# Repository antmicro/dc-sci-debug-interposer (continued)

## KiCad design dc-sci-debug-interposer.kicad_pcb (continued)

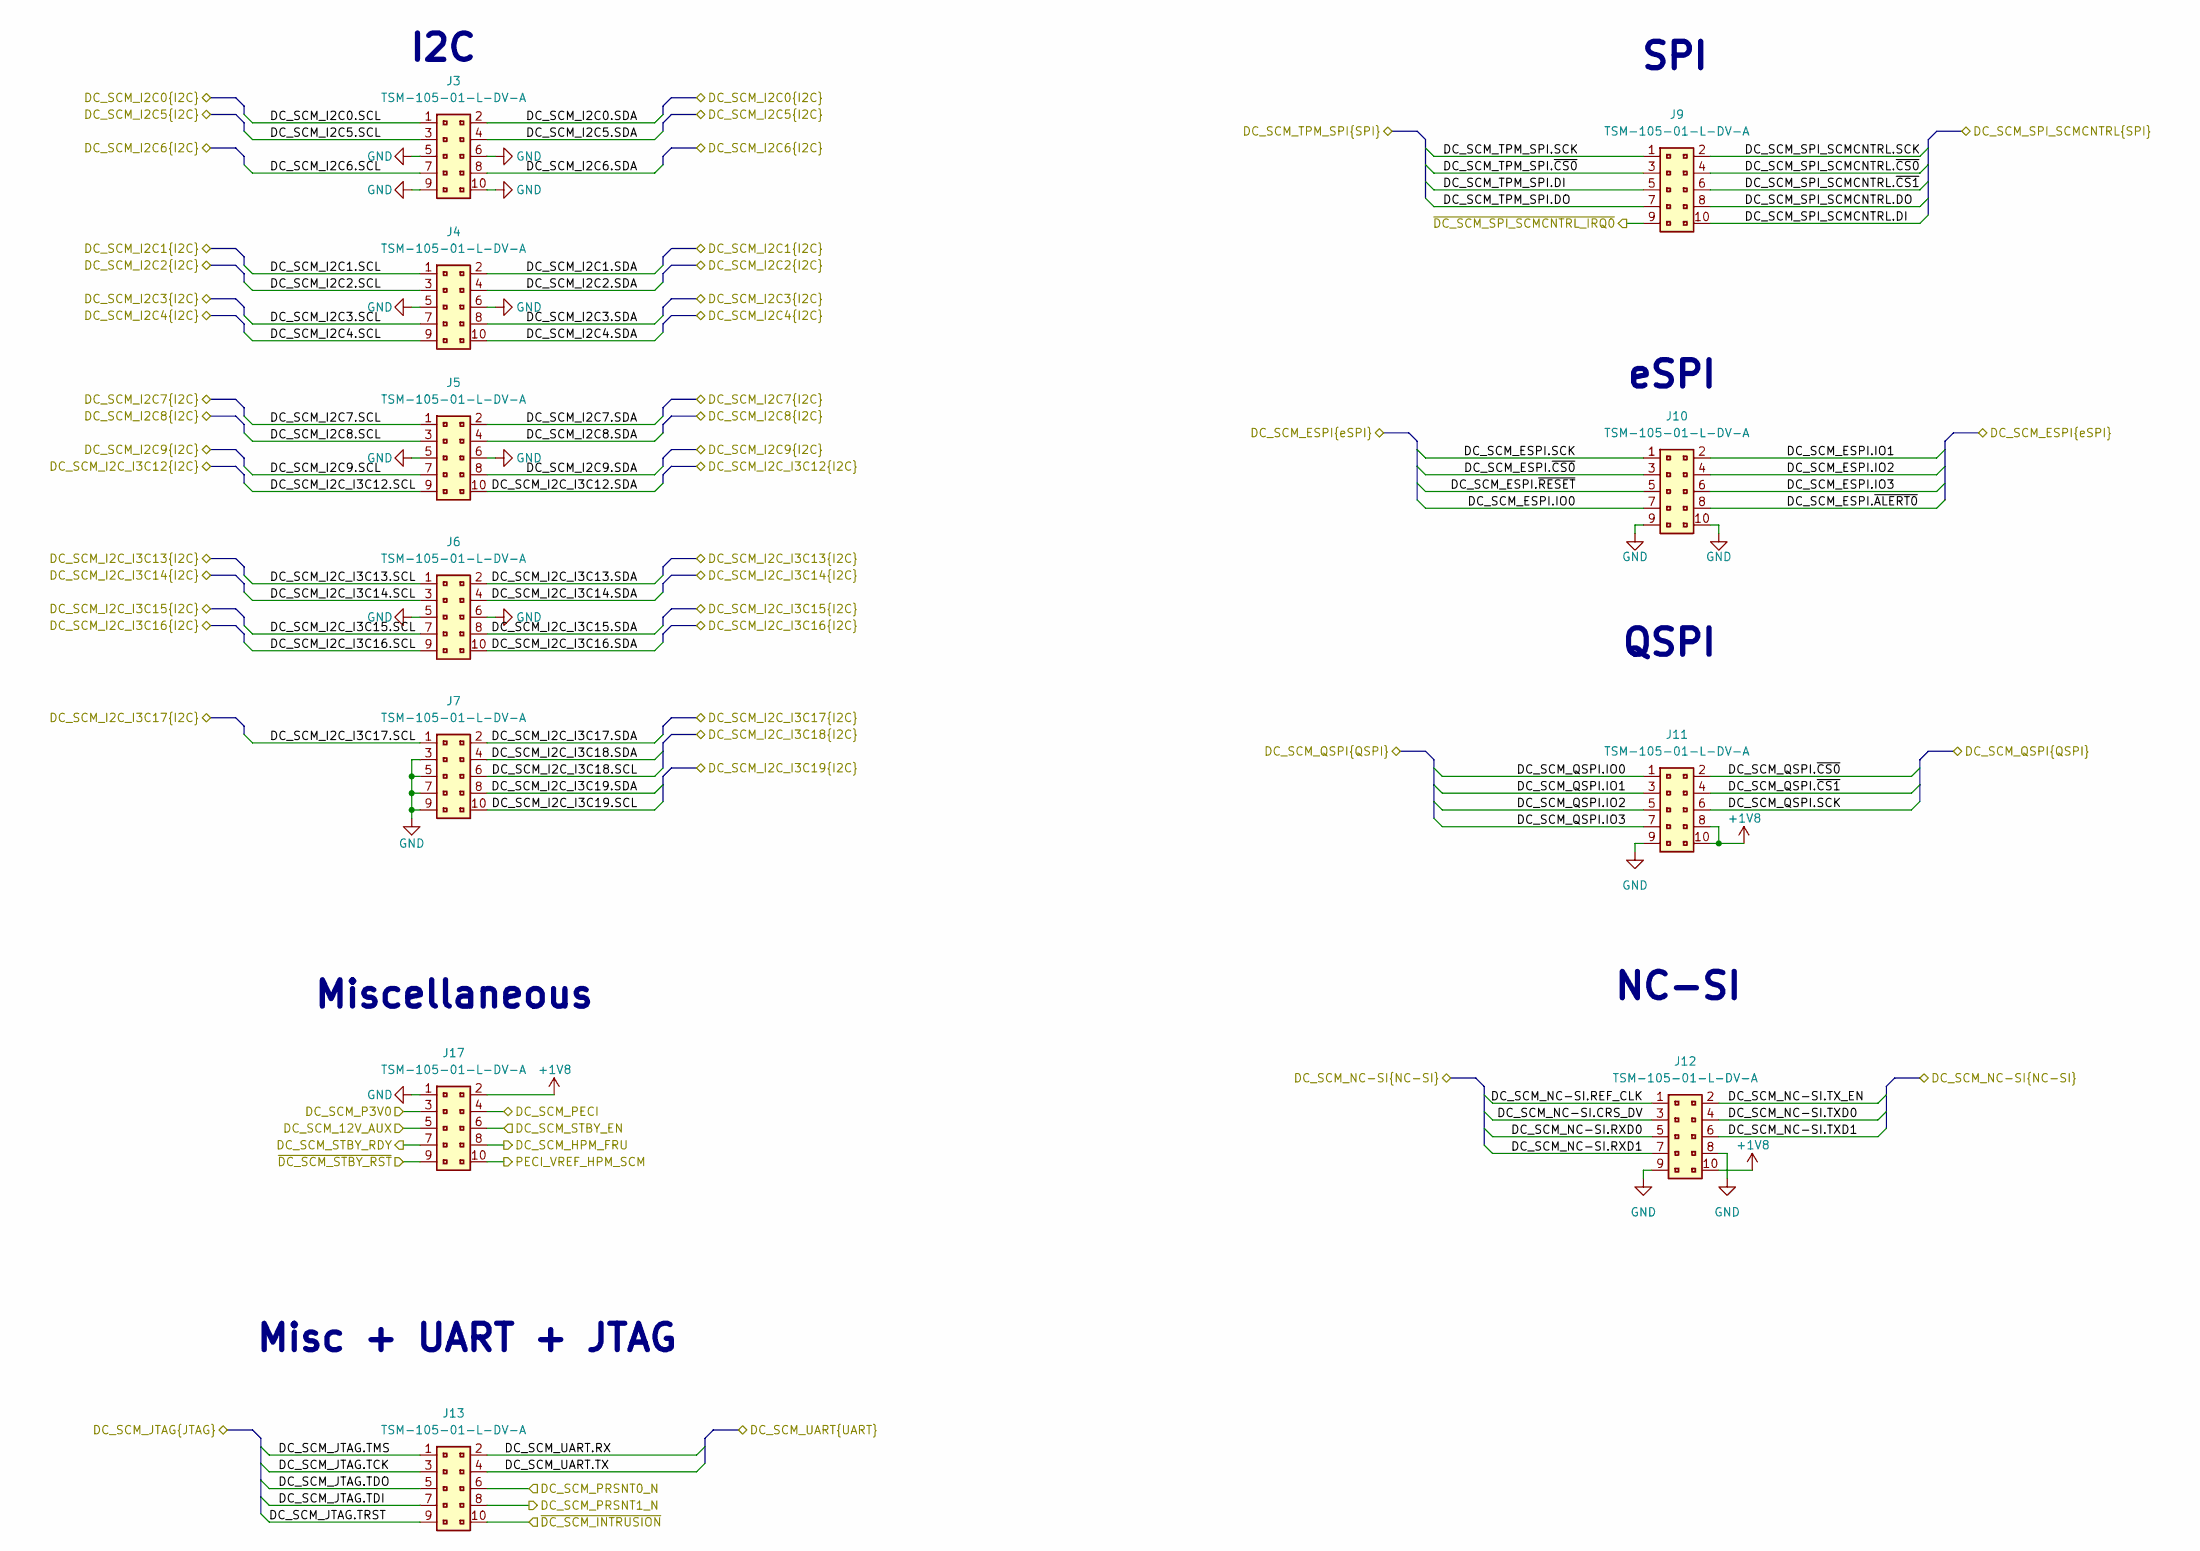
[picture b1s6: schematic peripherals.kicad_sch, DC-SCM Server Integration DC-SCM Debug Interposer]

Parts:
J3, J4, J5, J6, J7, J9, J10, J11, J12, J13, J17: PinHeader_2x5_P2.54mm_SMD; MPN TSM-105-01-L-DV-A

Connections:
+1V8: J11.8, J11.10, J12.10, J17.2; also elsewhere on the board
/DC-SCI edge connector/DC_SCM_12V_AUX: J17.5; also elsewhere on the board
/DC-SCI edge connector/DC_SCM_ESPI.IO0: J10.7; also elsewhere on the board
/DC-SCI edge connector/DC_SCM_ESPI.IO1: J10.2; also elsewhere on the board
/DC-SCI edge connector/DC_SCM_ESPI.IO2: J10.4; also elsewhere on the board
/DC-SCI edge connector/DC_SCM_ESPI.IO3: J10.6; also elsewhere on the board
/DC-SCI edge connector/DC_SCM_ESPI.SCK: J10.1; also elsewhere on the board
/DC-SCI edge connector/DC_SCM_ESPI.~ALERT0: J10.8; also elsewhere on the board
/DC-SCI edge connector/DC_SCM_ESPI.~CS0: J10.3; also elsewhere on the board
/DC-SCI edge connector/DC_SCM_ESPI.~RESET: J10.5; also elsewhere on the board
/DC-SCI edge connector/DC_SCM_HPM_FRU: J17.8; also elsewhere on the board
/DC-SCI edge connector/DC_SCM_I2C0.SCL: J3.1; also elsewhere on the board
/DC-SCI edge connector/DC_SCM_I2C0.SDA: J3.2; also elsewhere on the board
/DC-SCI edge connector/DC_SCM_I2C1.SCL: J4.1; also elsewhere on the board
/DC-SCI edge connector/DC_SCM_I2C1.SDA: J4.2; also elsewhere on the board
/DC-SCI edge connector/DC_SCM_I2C2.SCL: J4.3; also elsewhere on the board
/DC-SCI edge connector/DC_SCM_I2C2.SDA: J4.4; also elsewhere on the board
/DC-SCI edge connector/DC_SCM_I2C3.SCL: J4.7; also elsewhere on the board
/DC-SCI edge connector/DC_SCM_I2C3.SDA: J4.8; also elsewhere on the board
/DC-SCI edge connector/DC_SCM_I2C4.SCL: J4.9; also elsewhere on the board
/DC-SCI edge connector/DC_SCM_I2C4.SDA: J4.10; also elsewhere on the board
/DC-SCI edge connector/DC_SCM_I2C5.SCL: J3.3; also elsewhere on the board
/DC-SCI edge connector/DC_SCM_I2C5.SDA: J3.4; also elsewhere on the board
/DC-SCI edge connector/DC_SCM_I2C6.SCL: J3.7; also elsewhere on the board
/DC-SCI edge connector/DC_SCM_I2C6.SDA: J3.8; also elsewhere on the board
/DC-SCI edge connector/DC_SCM_I2C7.SCL: J5.1; also elsewhere on the board
/DC-SCI edge connector/DC_SCM_I2C7.SDA: J5.2; also elsewhere on the board
/DC-SCI edge connector/DC_SCM_I2C8.SCL: J5.3; also elsewhere on the board
/DC-SCI edge connector/DC_SCM_I2C8.SDA: J5.4; also elsewhere on the board
/DC-SCI edge connector/DC_SCM_I2C9.SCL: J5.7; also elsewhere on the board
/DC-SCI edge connector/DC_SCM_I2C9.SDA: J5.8; also elsewhere on the board
/DC-SCI edge connector/DC_SCM_I2C_I3C12.SCL: J5.9; also elsewhere on the board
/DC-SCI edge connector/DC_SCM_I2C_I3C12.SDA: J5.10; also elsewhere on the board
/DC-SCI edge connector/DC_SCM_I2C_I3C13.SCL: J6.1; also elsewhere on the board
/DC-SCI edge connector/DC_SCM_I2C_I3C13.SDA: J6.2; also elsewhere on the board
/DC-SCI edge connector/DC_SCM_I2C_I3C14.SCL: J6.3; also elsewhere on the board
/DC-SCI edge connector/DC_SCM_I2C_I3C14.SDA: J6.4; also elsewhere on the board
/DC-SCI edge connector/DC_SCM_I2C_I3C15.SCL: J6.7; also elsewhere on the board
/DC-SCI edge connector/DC_SCM_I2C_I3C15.SDA: J6.8; also elsewhere on the board
/DC-SCI edge connector/DC_SCM_I2C_I3C16.SCL: J6.9; also elsewhere on the board
/DC-SCI edge connector/DC_SCM_I2C_I3C16.SDA: J6.10; also elsewhere on the board
/DC-SCI edge connector/DC_SCM_I2C_I3C17.SCL: J7.1; also elsewhere on the board
/DC-SCI edge connector/DC_SCM_I2C_I3C17.SDA: J7.2; also elsewhere on the board
/DC-SCI edge connector/DC_SCM_I2C_I3C18.SCL: J7.6; also elsewhere on the board
/DC-SCI edge connector/DC_SCM_I2C_I3C18.SDA: J7.4; also elsewhere on the board
/DC-SCI edge connector/DC_SCM_I2C_I3C19.SCL: J7.10; also elsewhere on the board
/DC-SCI edge connector/DC_SCM_I2C_I3C19.SDA: J7.8; also elsewhere on the board
/DC-SCI edge connector/DC_SCM_JTAG.TCK: J13.3; also elsewhere on the board
/DC-SCI edge connector/DC_SCM_JTAG.TDI: J13.7; also elsewhere on the board
/DC-SCI edge connector/DC_SCM_JTAG.TDO: J13.5; also elsewhere on the board
/DC-SCI edge connector/DC_SCM_JTAG.TMS: J13.1; also elsewhere on the board
/DC-SCI edge connector/DC_SCM_JTAG.TRST: J13.9; also elsewhere on the board
/DC-SCI edge connector/DC_SCM_NC-SI.CRS_DV: J12.3; also elsewhere on the board
/DC-SCI edge connector/DC_SCM_NC-SI.REF_CLK: J12.1; also elsewhere on the board
/DC-SCI edge connector/DC_SCM_NC-SI.RXD0: J12.5; also elsewhere on the board
/DC-SCI edge connector/DC_SCM_NC-SI.RXD1: J12.7; also elsewhere on the board
/DC-SCI edge connector/DC_SCM_NC-SI.TXD0: J12.4; also elsewhere on the board
/DC-SCI edge connector/DC_SCM_NC-SI.TXD1: J12.6; also elsewhere on the board
/DC-SCI edge connector/DC_SCM_NC-SI.TX_EN: J12.2; also elsewhere on the board
/DC-SCI edge connector/DC_SCM_P3V0: J17.3; also elsewhere on the board
/DC-SCI edge connector/DC_SCM_PECI: J17.4; also elsewhere on the board
/DC-SCI edge connector/DC_SCM_PRSNT0_N: J13.6; also elsewhere on the board
/DC-SCI edge connector/DC_SCM_PRSNT1_N: J13.8; also elsewhere on the board
/DC-SCI edge connector/DC_SCM_QSPI.IO0: J11.1; also elsewhere on the board
/DC-SCI edge connector/DC_SCM_QSPI.IO1: J11.3; also elsewhere on the board
/DC-SCI edge connector/DC_SCM_QSPI.IO2: J11.5; also elsewhere on the board
/DC-SCI edge connector/DC_SCM_QSPI.IO3: J11.7; also elsewhere on the board
/DC-SCI edge connector/DC_SCM_QSPI.SCK: J11.6; also elsewhere on the board
/DC-SCI edge connector/DC_SCM_QSPI.~CS0: J11.2; also elsewhere on the board
/DC-SCI edge connector/DC_SCM_QSPI.~CS1: J11.4; also elsewhere on the board
/DC-SCI edge connector/DC_SCM_SPI_SCMCNTRL.DI: J9.10; also elsewhere on the board
/DC-SCI edge connector/DC_SCM_SPI_SCMCNTRL.DO: J9.8; also elsewhere on the board
/DC-SCI edge connector/DC_SCM_SPI_SCMCNTRL.SCK: J9.2; also elsewhere on the board
/DC-SCI edge connector/DC_SCM_SPI_SCMCNTRL.~CS0: J9.4; also elsewhere on the board
/DC-SCI edge connector/DC_SCM_SPI_SCMCNTRL.~CS1: J9.6; also elsewhere on the board
/DC-SCI edge connector/DC_SCM_STBY_EN: J17.6; also elsewhere on the board
/DC-SCI edge connector/DC_SCM_STBY_RDY: J17.7; also elsewhere on the board
/DC-SCI edge connector/DC_SCM_TPM_SPI.DI: J9.5; also elsewhere on the board
/DC-SCI edge connector/DC_SCM_TPM_SPI.DO: J9.7; also elsewhere on the board
/DC-SCI edge connector/DC_SCM_TPM_SPI.SCK: J9.1; also elsewhere on the board
/DC-SCI edge connector/DC_SCM_TPM_SPI.~CS0: J9.3; also elsewhere on the board
/DC-SCI edge connector/DC_SCM_UART.RX: J13.2; also elsewhere on the board
/DC-SCI edge connector/DC_SCM_UART.TX: J13.4; also elsewhere on the board
/DC-SCI edge connector/PECI_VREF_HPM_SCM: J17.10; also elsewhere on the board
/DC-SCI edge connector/~DC_SCM_INTRUSION: J13.10; also elsewhere on the board
/DC-SCI edge connector/~DC_SCM_SPI_SCMCNTRL_IRQ0: J9.9; also elsewhere on the board
/DC-SCI edge connector/~DC_SCM_STBY_RST: J17.9; also elsewhere on the board
GND: J3.5, J3.6, J3.9, J3.10, J4.5, J4.6, J5.5, J5.6, J6.5, J6.6, J7.3, J7.5, J7.7, J7.9, J10.9, J10.10, J11.9, J12.8, J12.9, J17.1; also elsewhere on the board

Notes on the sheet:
I2C
SPI
NC-SI
Misc + UART + JTAG
Miscellaneous
eSPI
QSPI

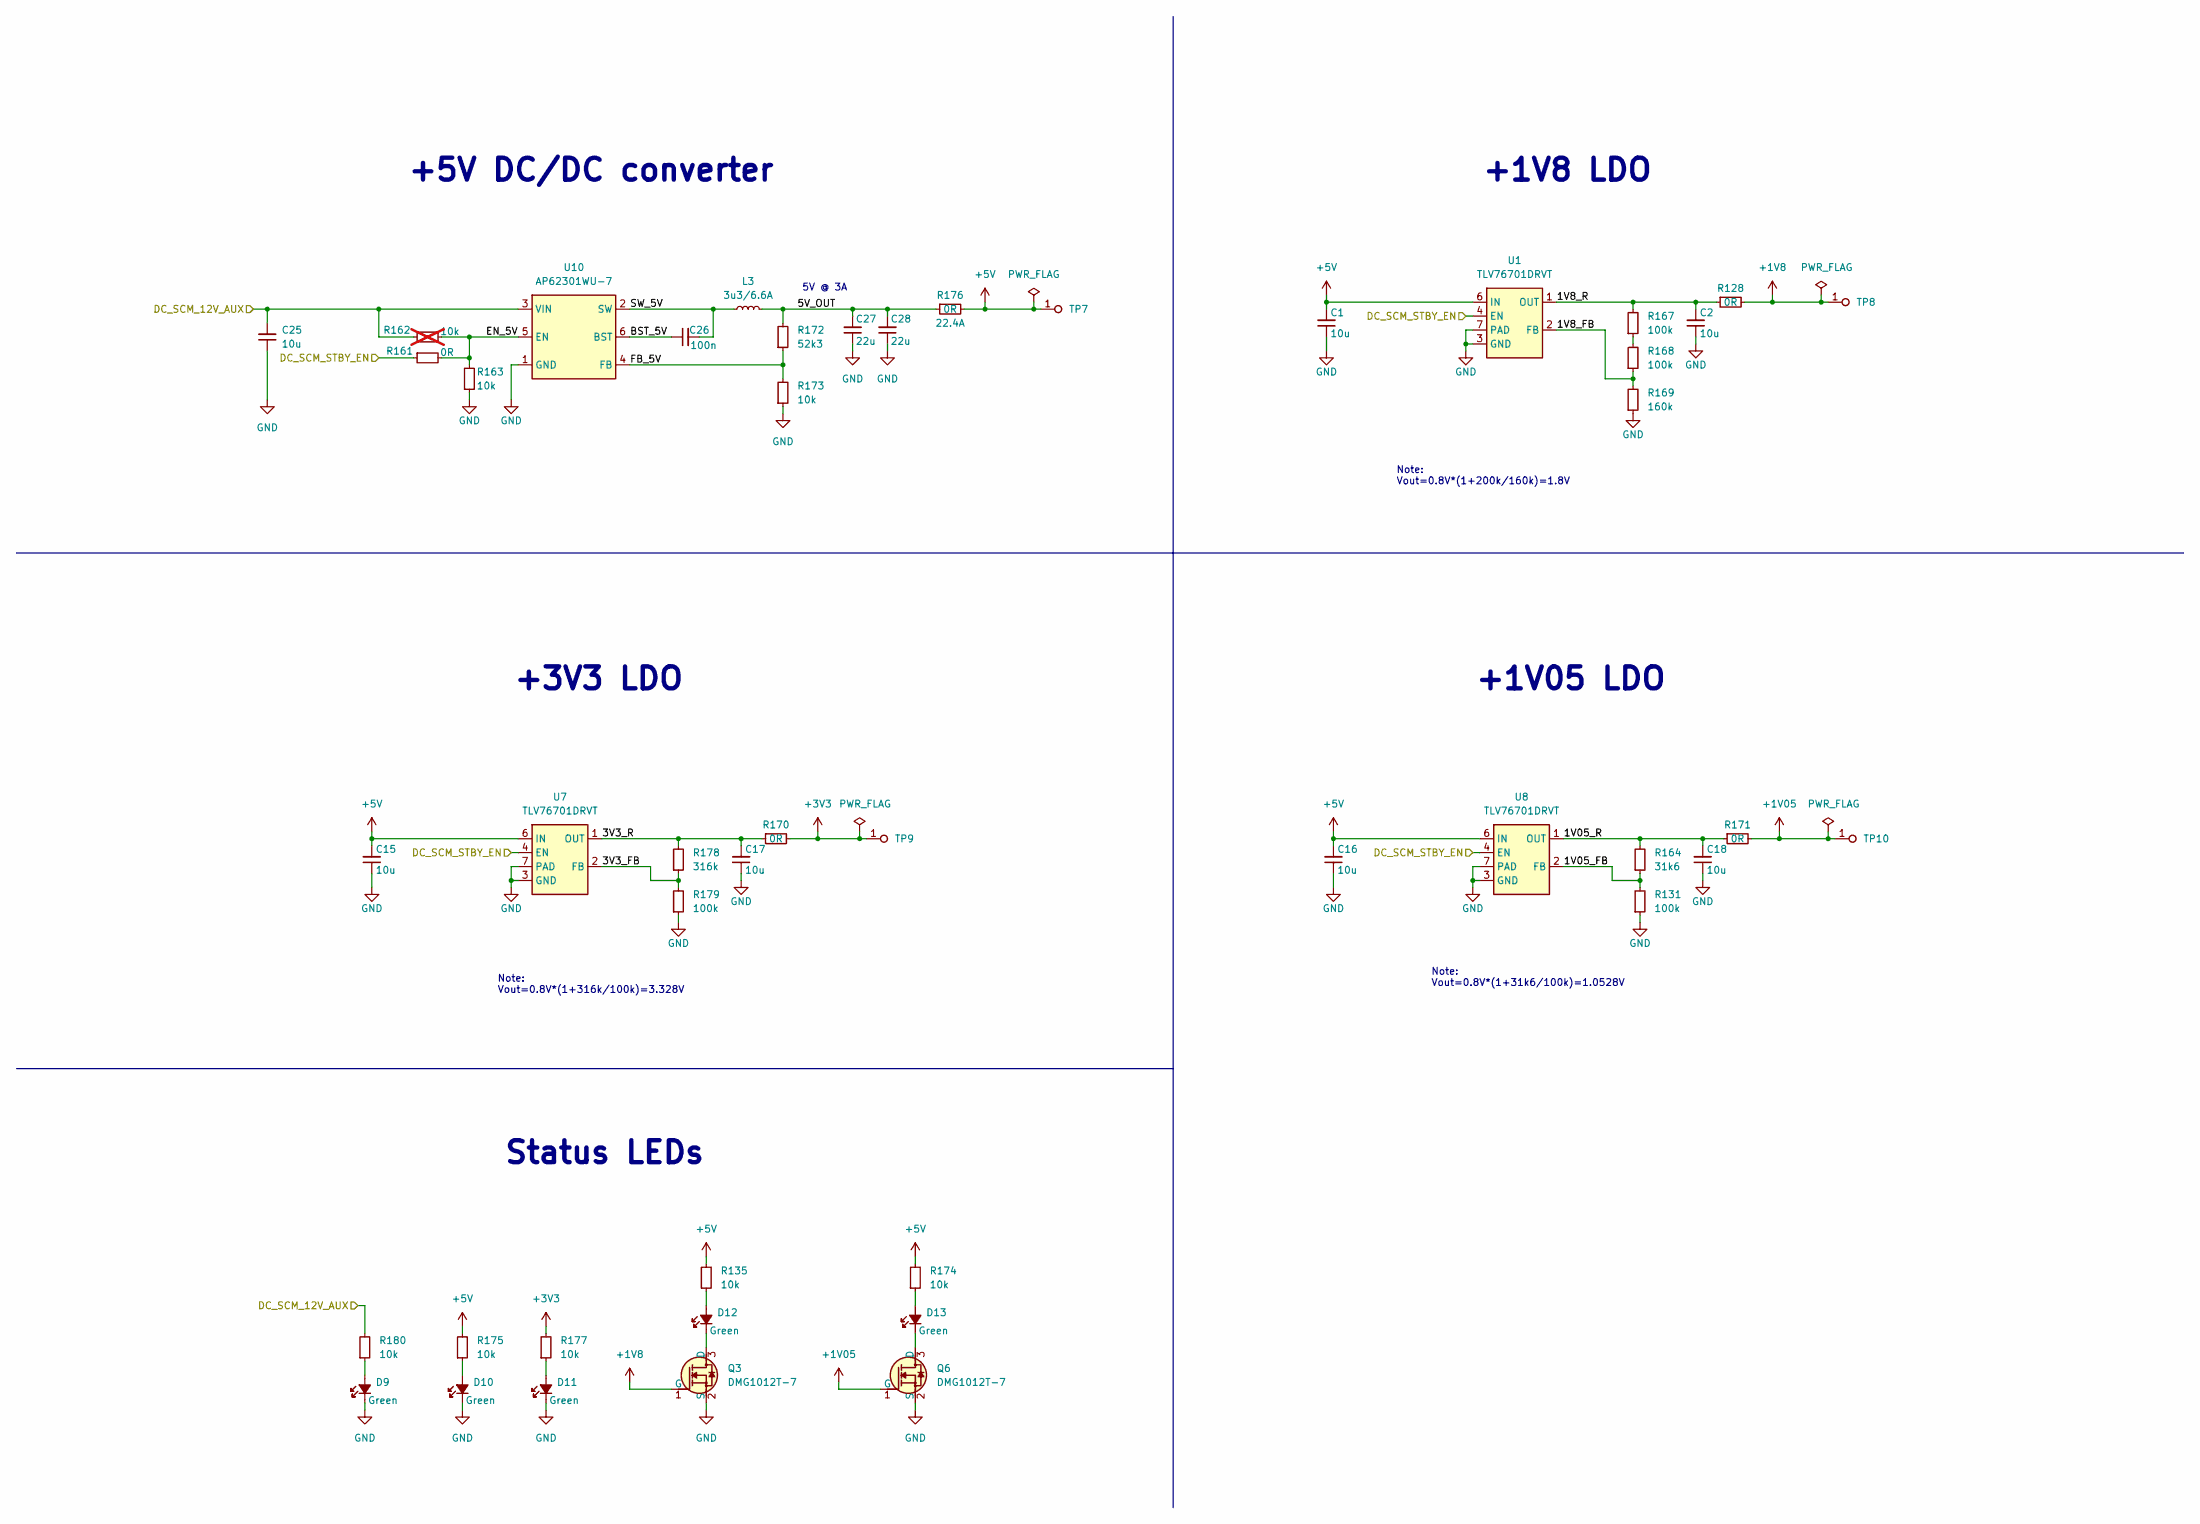
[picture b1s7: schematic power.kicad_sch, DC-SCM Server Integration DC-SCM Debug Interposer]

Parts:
C1, C2, C15, C16, C17, C18: C_10u_10V_0402; C_0402_1005Metric; Voltage 10V; MPN GRM155R61A106ME11D
C25: C_10u_16V_0603; C_0603_1608Metric; Voltage 16V; MPN GRM188C81C106MA73D
C26: C_100n_50V_X8L_0402; C_0402_1005Metric; Voltage 50V; MPN GCM155L8EH104KE07D
C27: C_22u_16V_0603; C_0603_1608Metric_EIA; Voltage 16V; MPN CL10A226MO7JZNC
C28: C_22u_0603; C_0603_1608Metric; MPN GRM188R60J226MEA0D
D9, D10, D11, D12, D13: LED_G_0603_LTST-C190GKT; LED_0603_1608Metric_G; MPN LTST-C190GKT
L3: L_3u3_6.6A_XEL4030; L_Coilcraft-XEL4030; MPN XEL4030-332MEC
Q3, Q6: DMG1012T-7; SOT-523; MPN DMG1012T-7
R128, R161, R170, R171: R_0R_0402; R_0402_1005Metric; MPN ERJ2GE0R00X
R131, R167, R168, R179: R_100k_0402; R_0402_1005Metric; Tolerance 1%; MPN CR0402-FX-1003GLF
R135, R163, R173, R174, R175, R177, R180: R_10k_0402; R_0402_1005Metric; Tolerance 1%; MPN CR0402-FX-1002GLF
R162: R_10k_0402; R_0402_1005Metric; Tolerance 1%; MPN CR0402-FX-1002GLF; not fitted
R164: R_31k6_0402; R_0402_1005Metric; Tolerance 1%; MPN CR0402-FX-3162GLF
R169: R_160k_0402; R_0402_1005Metric; Tolerance 1%; MPN CR0402-FX-1603GLF
R172: R_52k3_0402; R_0402_1005Metric; Tolerance 1%; MPN CR0402-FX-5232GLF
R176: R_0R_22.4A_0603; R_0603_1608Metric; Tolerance template_tolerance; MPN PMR03EZPJ000
R178: R_316k_0402; R_0402_1005Metric; Tolerance 1%; MPN CR0402-FX-3163GLF
TP7, TP8, TP9, TP10: TP_0.75mm_SMD; TP_SMD_0.75mm
U1, U7, U8: TLV76701_WSON; WSON-6-1EP_2x2mm_P0.65mm; MPN TLV76701DRVT
U10: AP62301_TSOT; TSOT23-6; MPN AP62301WU-7

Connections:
+1V05: Q6.1 (G), R171.2, TP10.1 (1_1); also elsewhere on the board
+1V8: Q3.1 (G), R128.2, TP8.1 (1_1); also elsewhere on the board
+3V3: R170.2, R177.2, TP9.1 (1_1); also elsewhere on the board
+5V: C1.2, C15.2, C16.2, R135.2, R174.2, R175.2, R176.2, TP7.1 (1_1), U1.6 (IN), U7.6 (IN), U8.6 (IN); also elsewhere on the board
/DC-SCI edge connector/DC_SCM_12V_AUX: C25.2, R162.2, R180.2, U10.3 (VIN); also elsewhere on the board
/DC-SCI edge connector/DC_SCM_STBY_EN: R161.1, U1.4 (EN), U7.4 (EN), U8.4 (EN); also elsewhere on the board
/Power/1V05_FB: R131.2, R164.1, U8.2 (FB)
/Power/1V05_R: C18.2, R164.2, R171.1, U8.1 (OUT)
/Power/1V8_FB: R168.1, R169.2, U1.2 (FB)
/Power/1V8_R: C2.2, R128.1, R167.2, U1.1 (OUT)
/Power/3V3_FB: R178.1, R179.2, U7.2 (FB)
/Power/3V3_R: C17.2, R170.1, R178.2, U7.1 (OUT)
/Power/5V_OUT: C27.2, C28.2, L3.2, R172.2, R176.1
/Power/BST_5V: C26.1, U10.6 (BST)
/Power/EN_5V: R161.2, R162.1, R163.2, U10.5 (EN)
/Power/FB_5V: R172.1, R173.2, U10.4 (FB)
/Power/SW_5V: C26.2, L3.1, U10.2 (SW)
GND: C1.1, C2.1, C15.1, C16.1, C17.1, C18.1, C25.1, C27.1, C28.1, D9.1 (C), D10.1 (C), D11.1 (C), Q3.2 (S), Q6.2 (S), R131.1, R163.1, R169.1, R173.1, R179.1, U1.3 (GND), U1.5 (GND), U1.7 (PAD), U7.3 (GND), U7.5 (GND), U7.7 (PAD), U8.3 (GND), U8.5 (GND), U8.7 (PAD), U10.1 (GND); also elsewhere on the board
unnamed: D9.2 (A), R180.1
unnamed: D10.2 (A), R175.1
unnamed: D11.2 (A), R177.1
unnamed: D12.2 (A), R135.1
unnamed: D12.1 (C), Q3.3 (D)
unnamed: D13.2 (A), R174.1
unnamed: D13.1 (C), Q6.3 (D)
unnamed: R167.1, R168.2

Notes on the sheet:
Note: Vout=0.8V*(1+31k6/100k)=1.0528V
Note: Vout=0.8V*(1+316k/100k)=3.328V
+1V8 LDO
Status LEDs
+5V DC/DC converter
5V @ 3A
+1V05 LDO
+3V3 LDO
Note: Vout=0.8V*(1+200k/160k)=1.8V

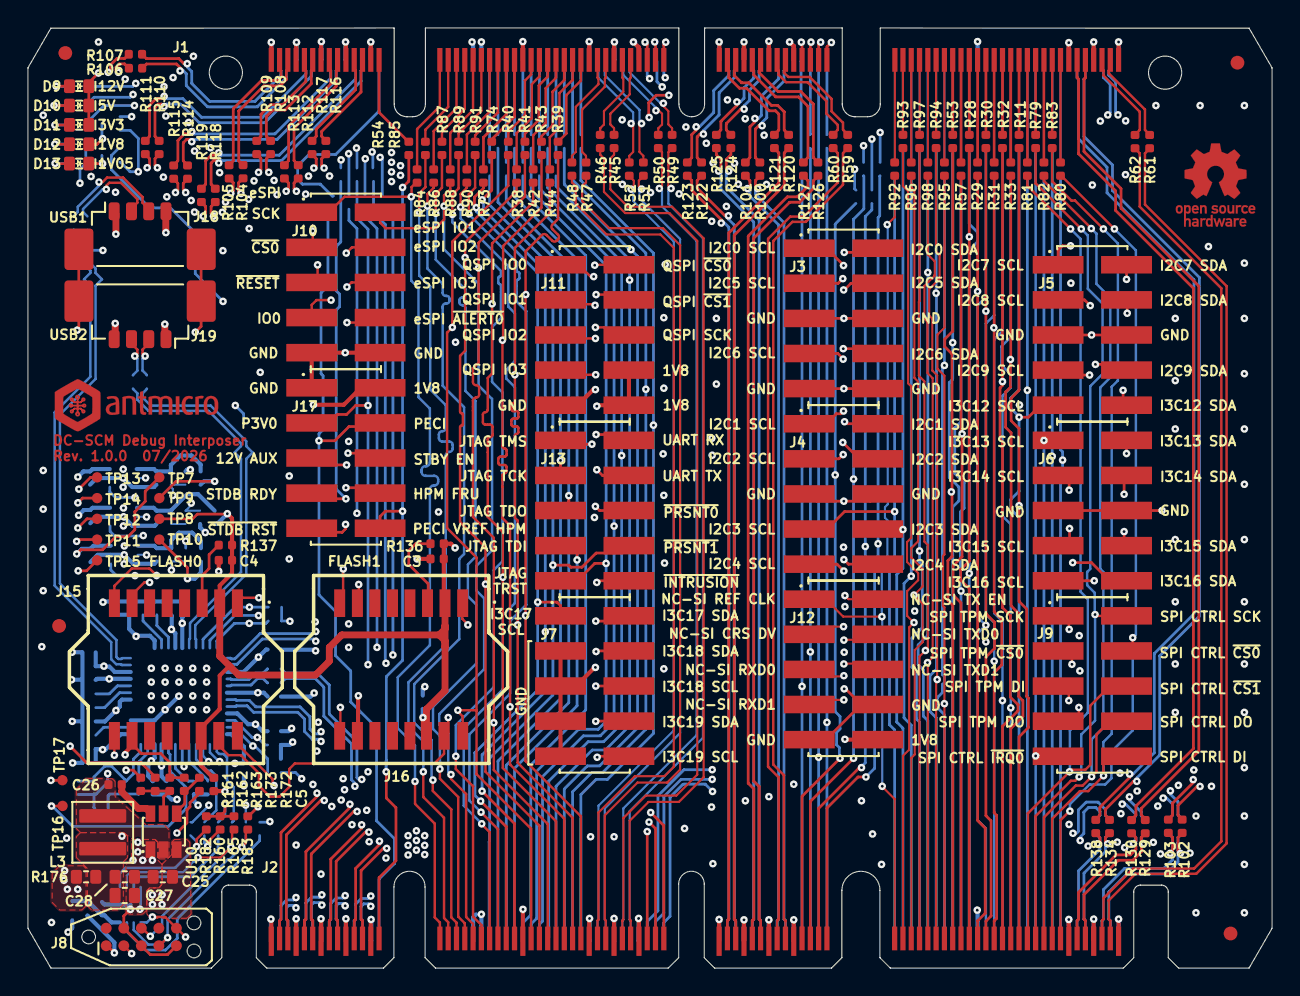
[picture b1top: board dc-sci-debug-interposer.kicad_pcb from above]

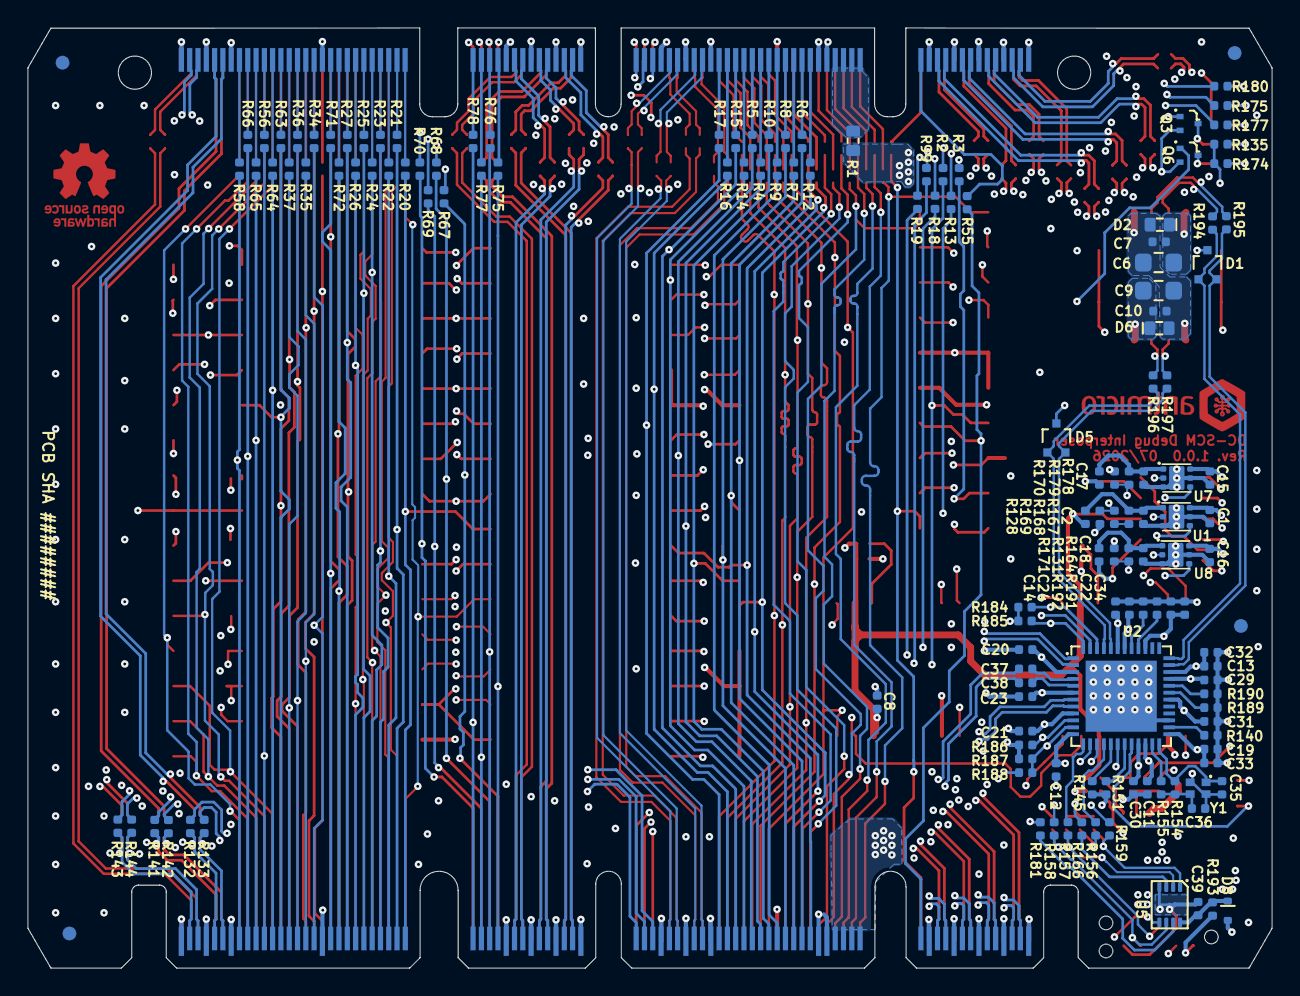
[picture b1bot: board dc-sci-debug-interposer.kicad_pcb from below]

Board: 8 copper layers, 90.0 x 68.0 mm, 285 parts (143 on the bottom side), 332 nets.
